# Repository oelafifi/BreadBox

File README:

This is a simple breadbox project based on arduino uno and TMP102 sensor

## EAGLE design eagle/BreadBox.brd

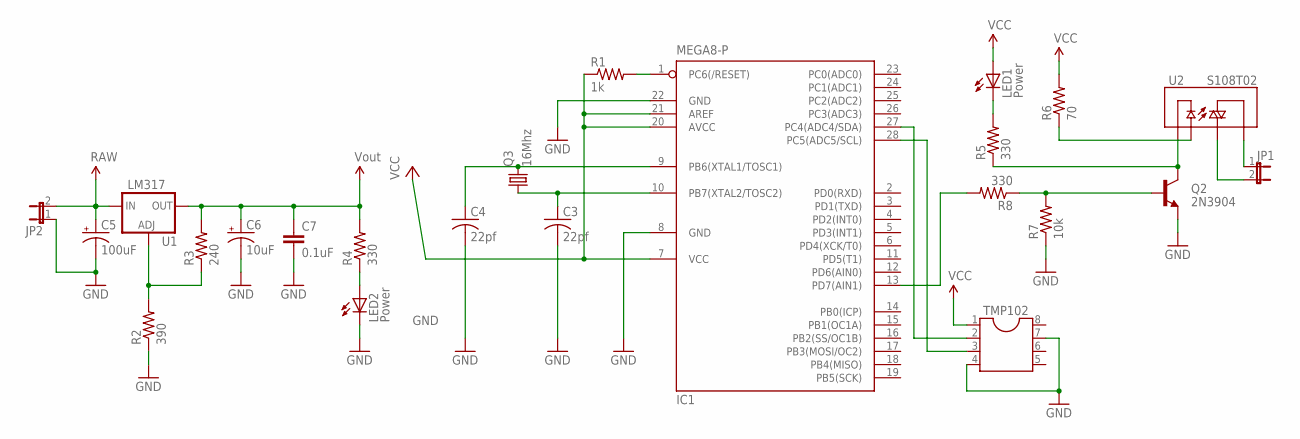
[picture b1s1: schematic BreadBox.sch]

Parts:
C3, C4: 22pf; C025-024X044
C5: 100uF; CPOL-RADIAL-100UF-25V
C6: 10uF; CPOL-RADIAL-10UF-25V
C7: 0.1uF; CAP-PTH-SMALL2
IC1: MEGA8-P; DIL28-3
JP1, JP2: JP1E; JP1
LED1, LED2: Power; LED5MM
Q2: 2N3904; TO-92
Q3: 16Mhz; HC18U-V
R1: 1k; 0207/10
R2: 390; AXIAL-0.3
R3: 240; AXIAL-0.3
R4, R5, R8: 330; AXIAL-0.3
R6: 70; AXIAL-0.3
R7: 10k; AXIAL-0.3
TMP102: DIL8S; SOCKET-08
U1: LM317; TO220-ADJ
U2: S108T02; RELAY-S108T02

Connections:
GND: C3.2, C4.2, C5.2 (-), C6.2 (-), C7.2, IC1.8 (GND), IC1.22 (GND), JP2.1, LED2.K (C), Q2.1 (E), R2.P$1 (1), R7.P$1 (1), TMP102.4, TMP102.7
unnamed: JP1.1, U2.1 (T1)
unnamed: Q2.2 (B), R7.P$2 (2), R8.P$1 (1)
unnamed: C4.1, IC1.9 (PB6(XTAL1/TOSC1)), Q3.2
unnamed: Q2.3 (C), R5.P$1 (1), U2.4 (-)
unnamed: C3.1, IC1.10 (PB7(XTAL2/TOSC2)), Q3.1
unnamed: R2.P$2 (2), R3.P$1 (1), U1.ADJ
unnamed: LED2.A, R4.P$1 (1)
unnamed: IC1.1 (PC6(/RESET)), R1.2
unnamed: R6.P$1 (1), U2.3 (+)
unnamed: LED1.K (C), R5.P$2 (2)
unnamed: IC1.13 (PD7(AIN1)), R8.P$2 (2)
unnamed: IC1.28 (PC5(ADC5/SCL)), TMP102.3
unnamed: IC1.27 (PC4(ADC4/SDA)), TMP102.2
unnamed: JP1.2, U2.2 (T2)
RAW: C5.1 (+), JP2.2, U1.IN
VCC: C6.1 (+), C7.1, IC1.7 (VCC), IC1.20 (AVCC), IC1.21 (AREF), LED1.A, R1.1, R3.P$2 (2), R4.P$2 (2), R6.P$2 (2), TMP102.1, U1.OUT

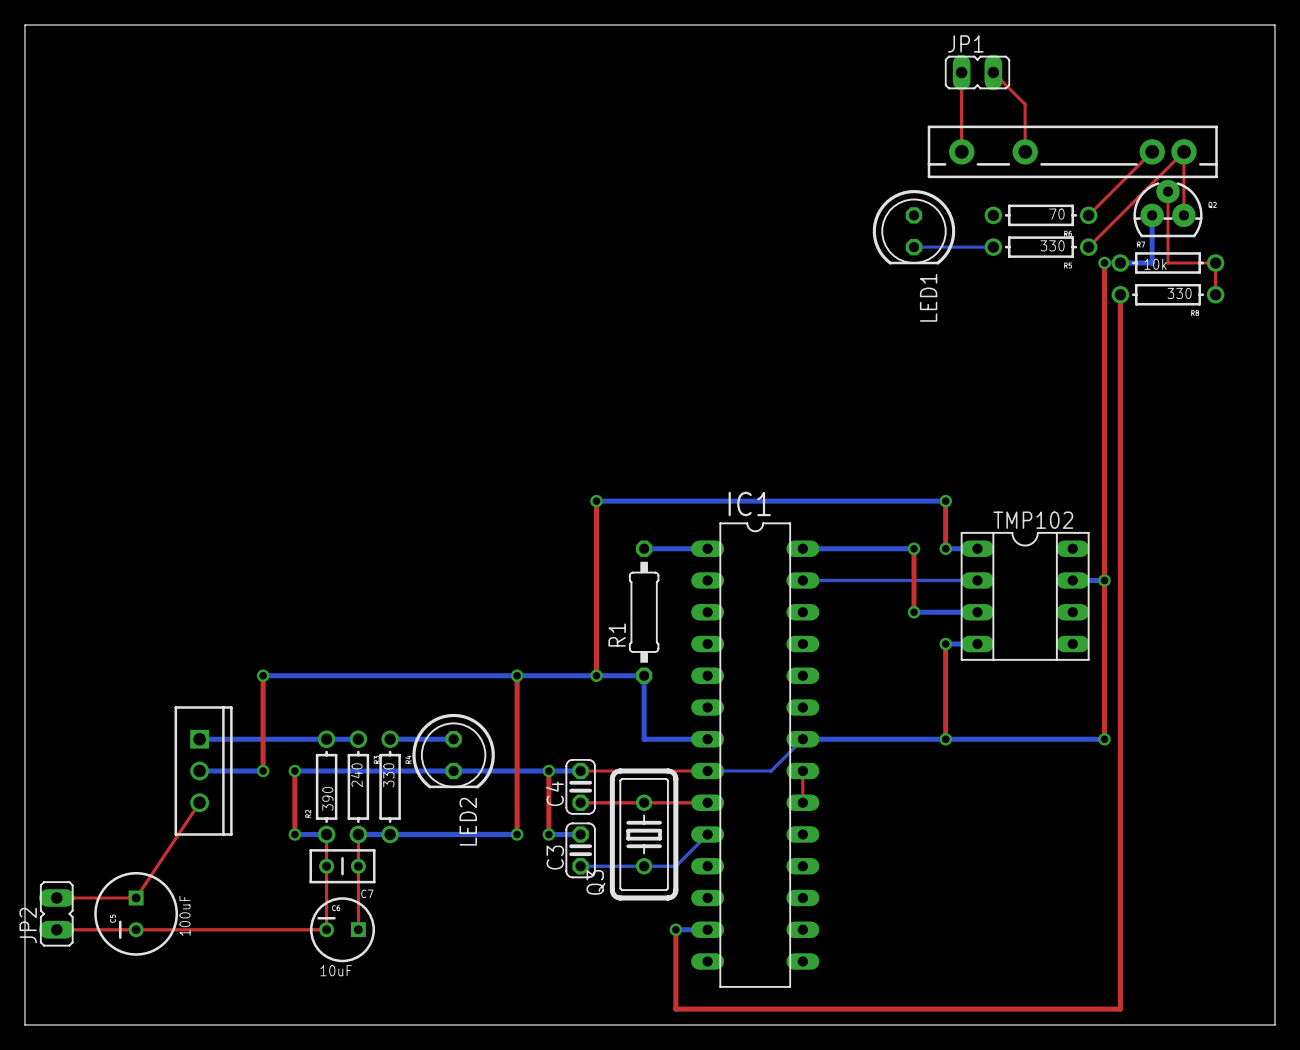
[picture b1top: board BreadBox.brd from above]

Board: 2 copper layers, 100.0 x 80.0 mm, 23 parts (0 on the bottom side), 17 nets.
